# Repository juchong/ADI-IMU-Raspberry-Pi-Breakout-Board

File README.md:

# ADI IMU Raspberry Pi Breakout Board
A simple Raspberry Pi breakout board (hat) for Analog Devices IMUs.

This board makes interfacing ADI IMUs with any platform that has a 40-pin connector compatible with the Raspberry Pi standard. 

## Design Features

This breakout board includes features that offer flexibility and expand compatibility with platforms beyond the Raspberry Pi and Jetson Nano. Features include:

1. Compatible with "compact" and "high-performance" ADI IMU families
   1. ADIS1647x
   2. ADIS1650x
   3. ADIS1648x
   4. ADIS1649x
2. Includes solder pads and resistor networks that enable making the following changes
   1. Sharing SPI1 between both sensors, or separating each sensor to it's own port (SPI1 and SPI2)
   2. Connecting the IMU VDD directly to the 5V supply
3. Includes a jumper that bypasses the onboard 3.3V regulator 

## Build Your Own

The PCB design is open-source and licensed under the MIT License. Copies of this circuit board may be purchased from OshPark [here](https://oshpark.com/shared_projects/AxJJlTrH).

| Designator     | Value              | Sub Allowed? |
| -------------- | ------------------ | ------------ |
| J1             | PPTC202LFBN-RC     | Y            |
| J2             | CLM-112-02-L-D     | N            |
| J3             | A3-16PA-2SV(71)    | Y            |
| J4             | 68000-203HLF       | Y            |
| U1             | ADM7172ACPZ-3.3-R7 | N            |
| C1, C2         | 10uF, 0805, 10V    | Y            |
| C3, C4         | 1uF, 0603, 10V     | Y            |
| R1, R2, R3, R4 | 0 ohm, 0603        | Y            |

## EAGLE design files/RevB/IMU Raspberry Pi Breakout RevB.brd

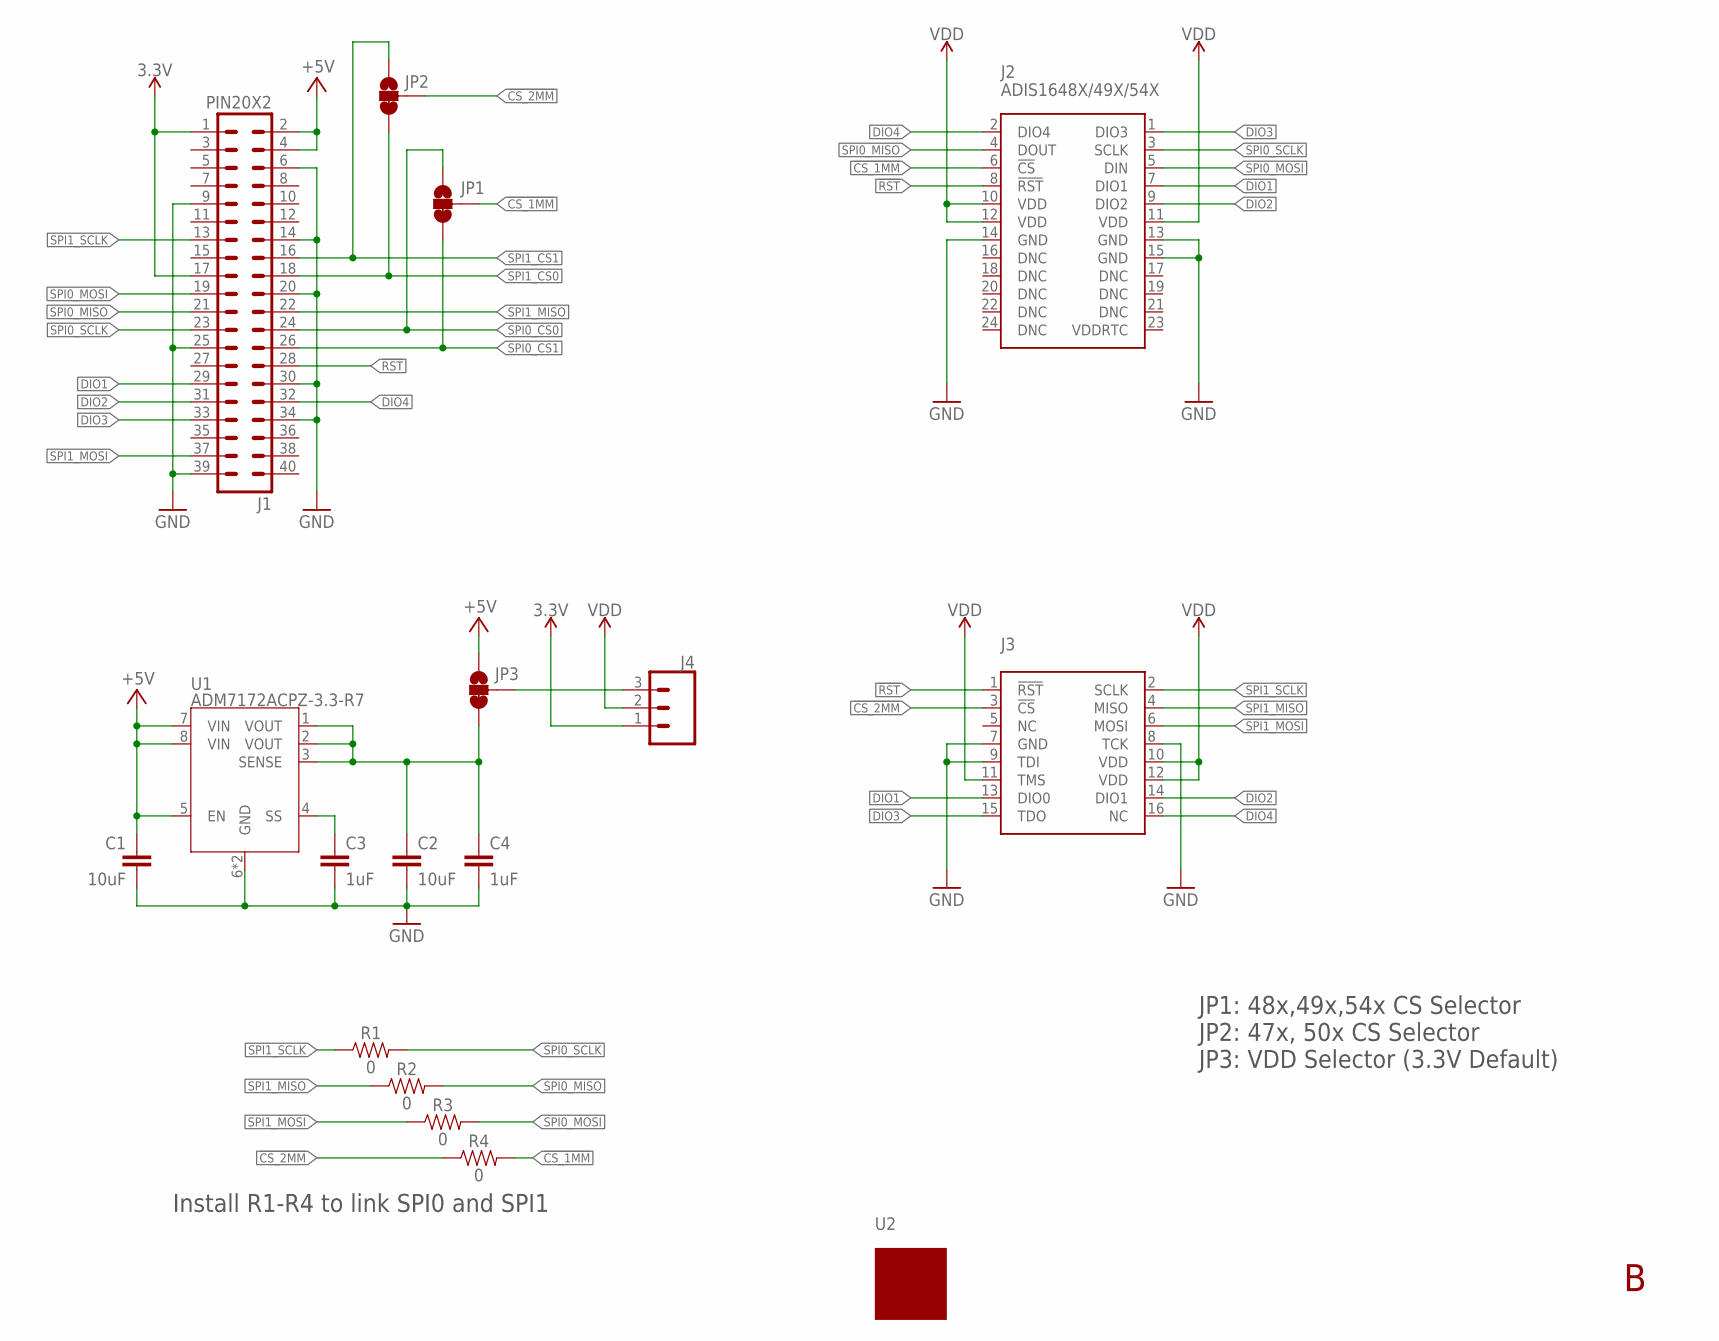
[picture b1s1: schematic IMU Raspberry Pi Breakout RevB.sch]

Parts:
C1, C2: 10uF; 0805
C3, C4: 1uF; 0603
J1: PIN20X2; PIN_20X2
J2: ADIS1648X/49X/54X; ADIS1648X-TAPPED
J3: ADIS_EVAL_16PIN_2MM; A3-16PA-2SV(71)-TOP
J4: 455-1750-1-ND; 1X03
JP1, JP2, JP3: JUMPER-SMT_3_1-NC_TRACE_SILK; SMT-JUMPER_3_1-NC_TRACE_SILK
R1, R2, R3, R4: 0; 0603
U1: ADM7172ACPZ-3.3-R7; LFCSP-8
U2: ADIS16XXX_COUPON

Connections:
3.3V: J1.1, J1.17, J4.1
!CS_1MM: J2.6 (!CS), JP1.2, R4.2
!CS_2MM: J3.3 (!CS), JP2.2, R4.1
!RST: J1.28, J2.8 (!RST), J3.1 (!RST)
+5V: C1.1, J1.2, J1.4, JP3.1, U1.5 (EN), U1.7 (VIN), U1.8 (VIN)
DIO1: J1.29, J2.7 (DIO1), J3.13 (DIO0)
DIO2: J1.31, J2.9 (DIO2), J3.14 (DIO1)
DIO3: J1.33, J2.1 (DIO3), J3.15 (TDO)
DIO4: J1.32, J2.2 (DIO4), J3.16 (NC)
GND: C1.2, C2.2, C3.2, C4.2, J1.6, J1.9, J1.14, J1.20, J1.25, J1.30, J1.34, J1.39, J2.13 (GND), J2.14 (GND), J2.15 (GND), J3.7 (GND), J3.8 (TCK), J3.9 (TDI), U1.6 (GND), U1.9 (GND)
unnamed: C2.1, C4.1, JP3.3, U1.1 (VOUT), U1.2 (VOUT), U1.3 (SENSE)
unnamed: J4.3, JP3.2
unnamed: C3.1, U1.4 (SS)
SPI0_CS0: J1.24, JP1.1
SPI0_CS1: J1.26, JP1.3
SPI0_MISO: J1.21, J2.4 (DOUT), R2.2
SPI0_MOSI: J1.19, J2.5 (DIN), R3.2
SPI0_SCLK: J1.23, J2.3 (SCLK), R1.2
SPI1_CS0: J1.18, JP2.3
SPI1_CS1: J1.16, JP2.1
SPI1_MISO: J1.22, J3.4 (MISO), R2.1
SPI1_MOSI: J1.37, J3.6 (MOSI), R3.1
SPI1_SCLK: J1.13, J3.2 (SCLK), R1.1
VDD: J2.10 (VDD), J2.11 (VDD), J2.12 (VDD), J3.10 (VDD), J3.11 (TMS), J3.12 (VDD), J4.2

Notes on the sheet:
JP1: 48x,49x,54x CS Selector JP2: 47x, 50x CS Selector JP3: VDD Selector (3.3V Default)
Install R1-R4 to link SPI0 and SPI1

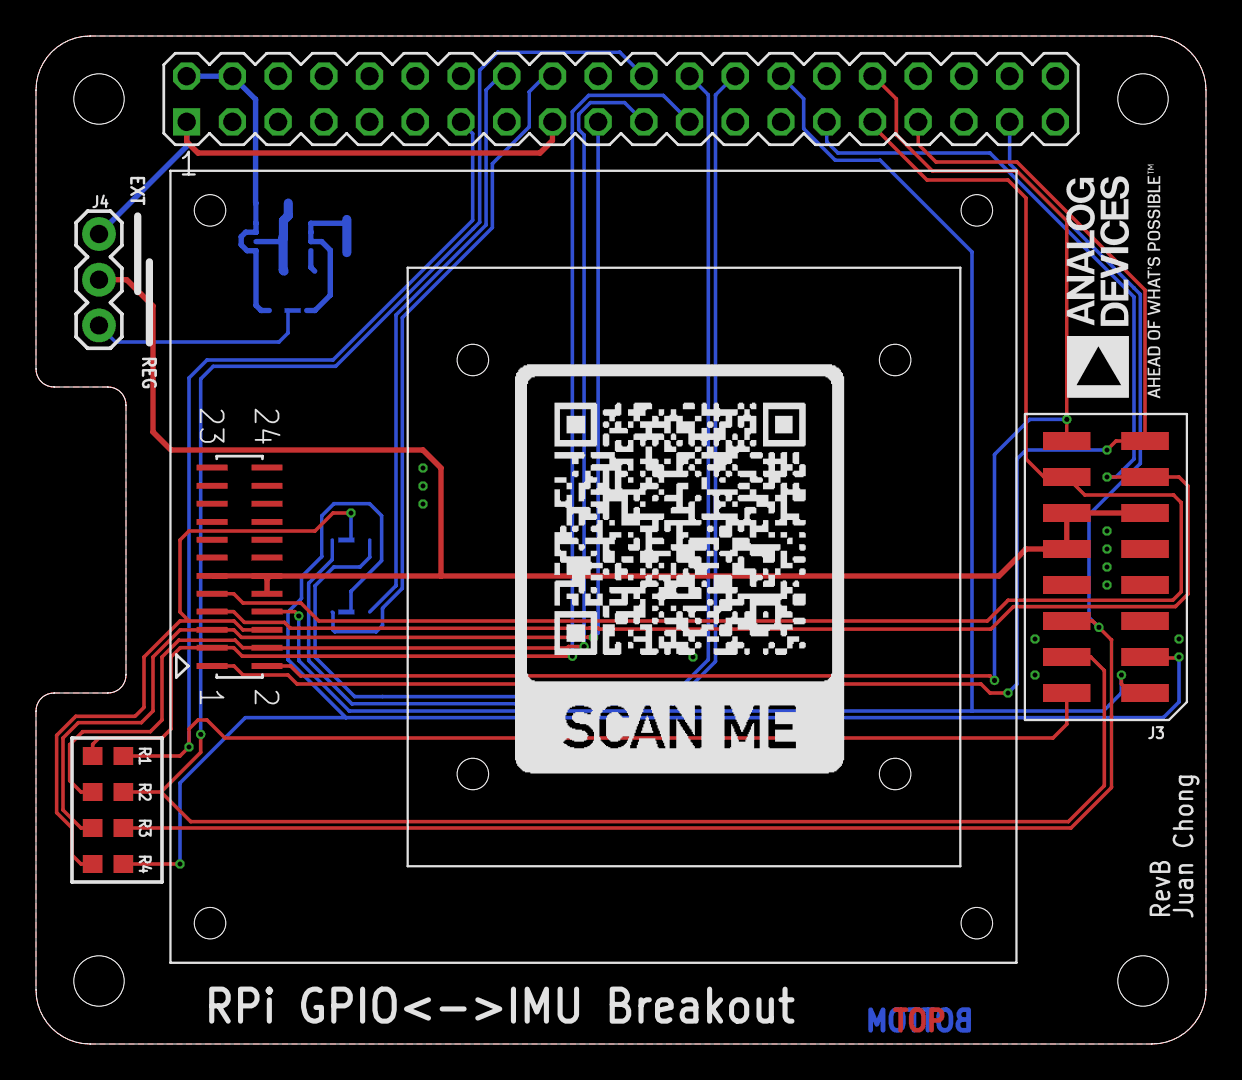
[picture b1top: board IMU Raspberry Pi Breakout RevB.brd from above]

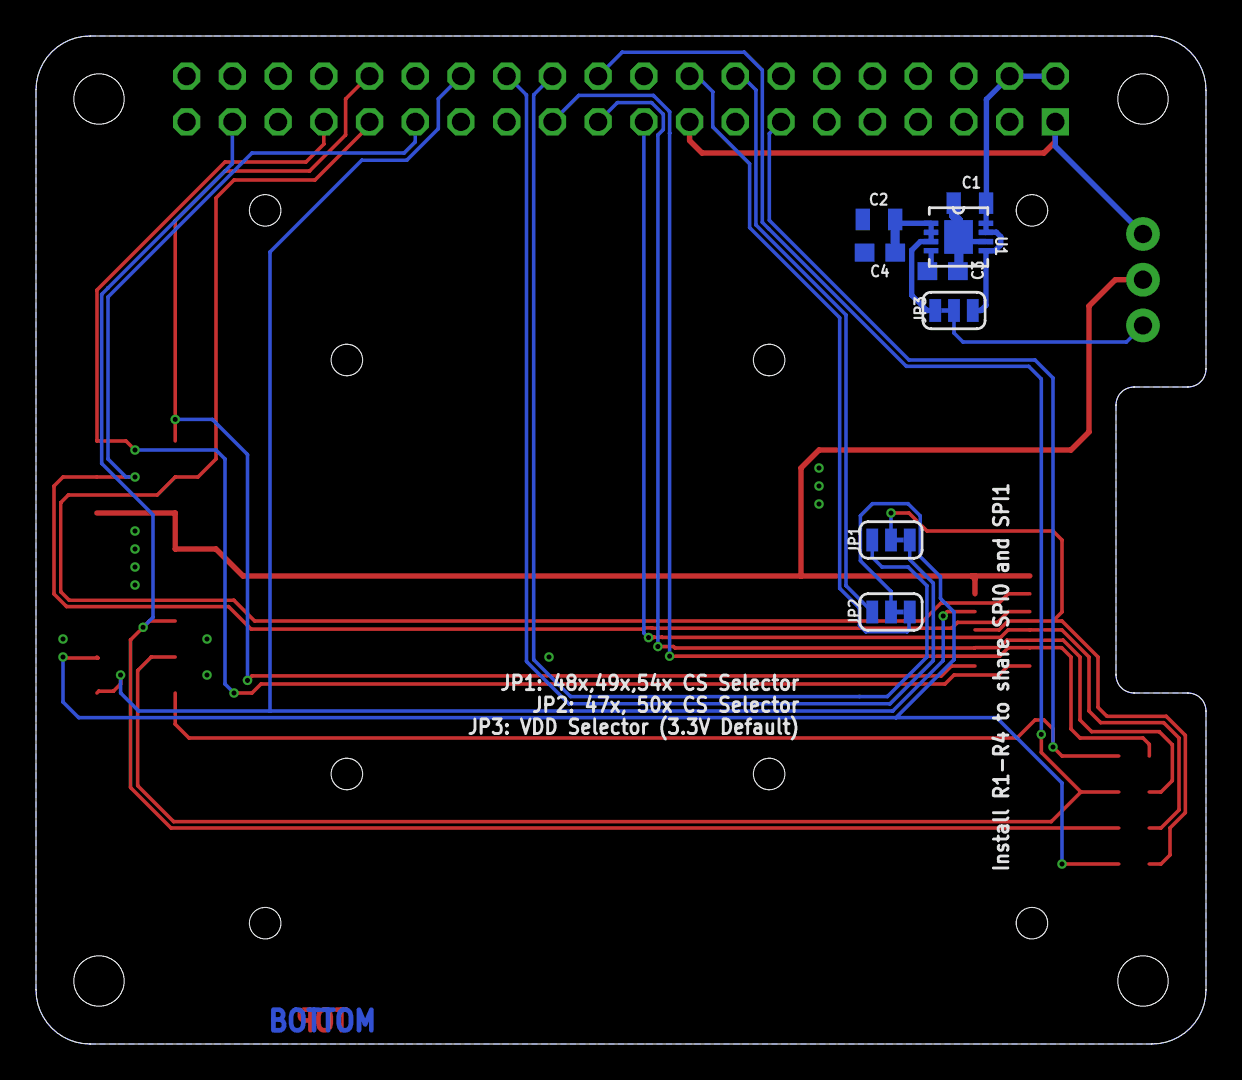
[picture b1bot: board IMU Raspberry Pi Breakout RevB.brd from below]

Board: 2 copper layers, 65.0 x 56.0 mm, 17 parts (8 on the bottom side), 24 nets.

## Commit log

2020-09-26 Updated design to include resistors that link SPI1 to SPI0. Improved silkscreen art.
2023-10-18 Added Rev A
2023-10-18 Moved pdfs

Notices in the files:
parts and their libraries:
ADI_iSensor_Footprints: Licensing: Creative Commons ShareAlike 4.0 International - https://creativecommons.org/licenses/by-sa/4.0
